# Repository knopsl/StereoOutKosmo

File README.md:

# Stereo output / Kosmo

Stereo output synthesizer module in Kosmo format.

This is somewhat based on the [Barton Stereo Outs](https://www.bartonmusicalcircuits.com/stereoouts/index.html)  module. There are four AC coupled inputs with pan and level controls. 

The headphone output section is based on the LM4808 datasheet circuit. This is an SMD (SOIC-8) part; all other components are through hole.

I've built this but my mechanical design was frankly stupid. I ended up kludging it together in a somewhat horrible way. I have eliminated the PCB design file and Gerbers from this repository; do better ones yourself! The circuit design is fine as far as I can see. So is the front panel except the slider mounting screws holes would be eliminated if I were to do it over.

## Photo

## Documentation:

* [Schematic](Docs/ao_output.pdf)
* [BOM](Docs/ao_output_bom.md)

## Submodules

This repo uses submodules aoKicad and Kosmo_panel, which provide needed libaries for KiCad. To clone:

```
git clone git@github.com:holmesrichards/audiomixer.git
git submodule init
git submodule update
```

Alternatively do

```
git clone --recurse-submodules git@github.com:holmesrichards/audiomixer.git
```

Or if you download the repository as a zip file, you must also click on the "aoKicad" and "Kosmo\_panel" links on the GitHub page (they'll have "@ something" after them) and download them as separate zip files which you can unzip into this repo's aoKicad and Kosmo\_panel directories.

If desired, copy the files from aoKicad and Kosmo\_panel to wherever you prefer (your KiCad user library directory, for instance, if you have one). Then in KiCad, add symbol libraries 

```
aoKicad/ao_symbols
Kosmo_panel/Kosmo
```
and footprint libraries 
```
aoKicad/ao_tht
Kosmo_panel/Kosmo_panel.
```

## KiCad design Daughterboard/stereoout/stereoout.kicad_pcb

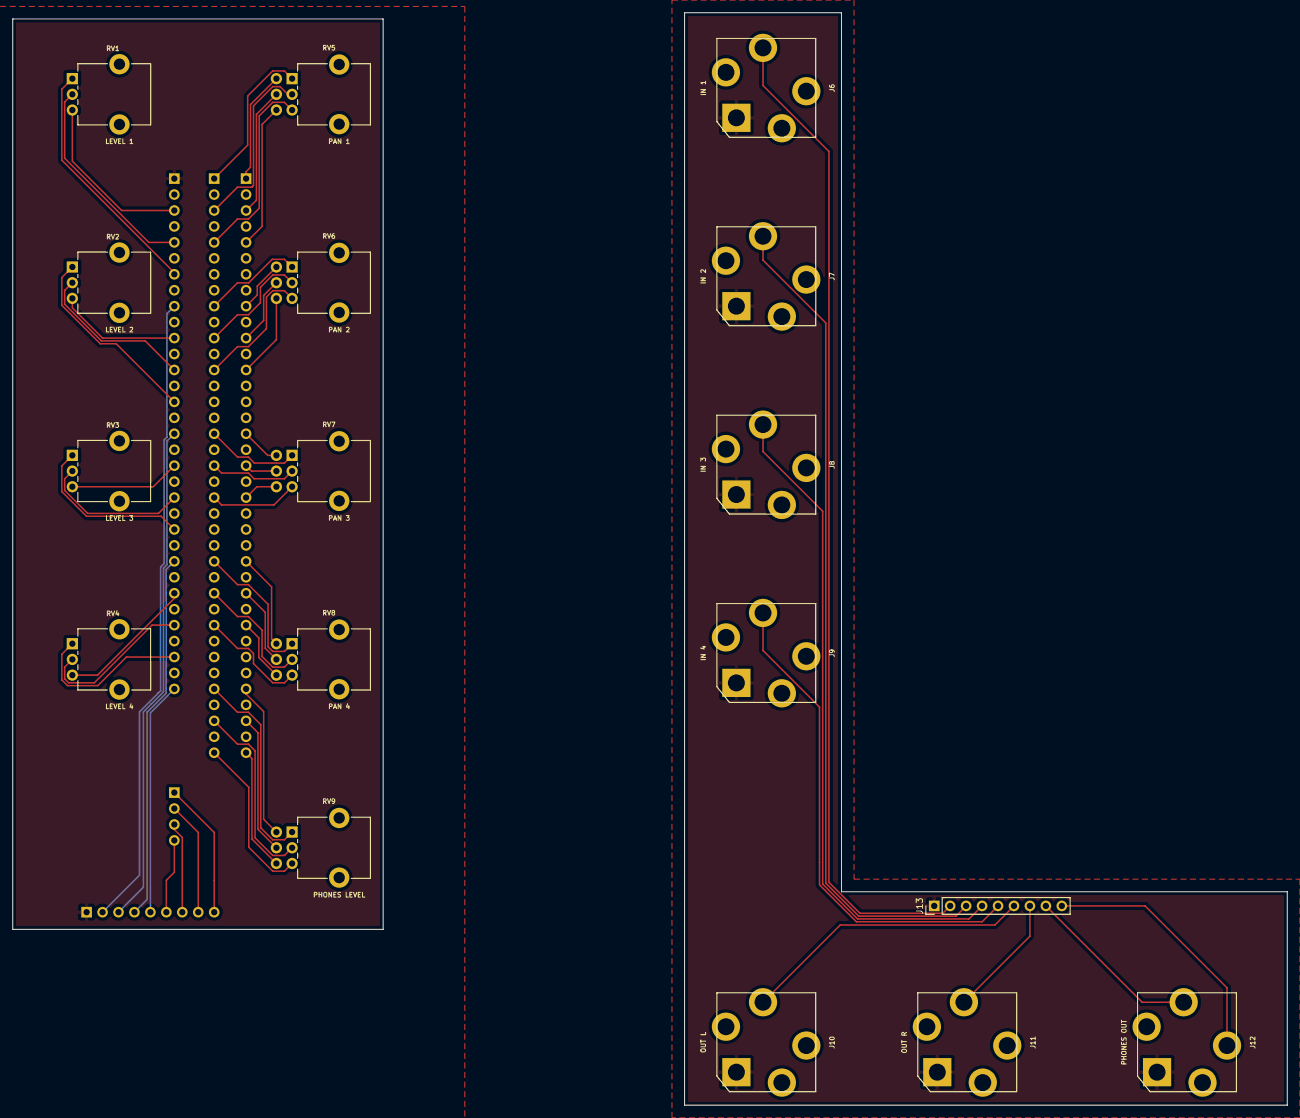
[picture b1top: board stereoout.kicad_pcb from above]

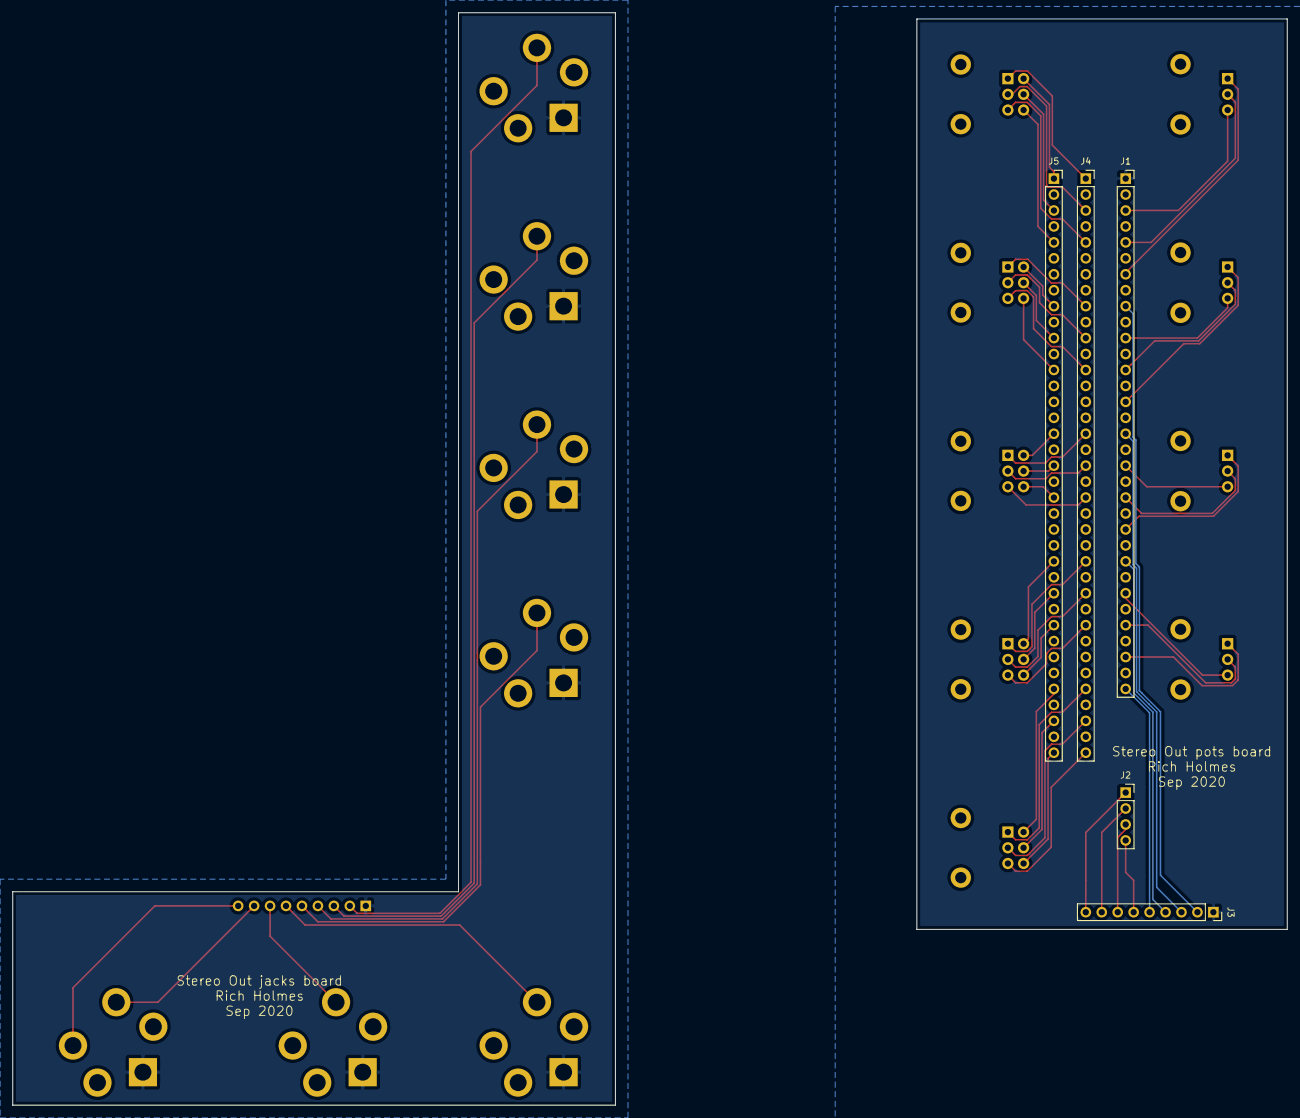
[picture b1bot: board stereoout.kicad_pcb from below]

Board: 2 copper layers, 203.0 x 174.0 mm, 22 parts (5 on the bottom side), 59 nets.

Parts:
J1: Conn_01x33; PinSocket_1x33_P2.54mm_Vertical
J2: Conn_01x04; PinSocket_1x04_P2.54mm_Vertical
J3: Conn_01x09; PinSocket_1x09_P2.54mm_Vertical
J4, J5: Conn_01x37; PinSocket_1x37_P2.54mm_Vertical
J6, J7, J8, J9, J10, J11: AudioJack2; Jack_6.35mm_PJ_629HAN
J12: AudioJack3; Jack_6.35mm_PJ_629HAN
J13: Conn_01x09; PinHeader_1x09_P2.54mm_Vertical
RV1, RV2, RV3, RV4: R_POT; Potentiometer_Alpha_RD901F-40-00D_Single_Vertical_CircularH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
RV5, RV6, RV7, RV8, RV9: R_POT; Potentiometer_Alpha_RD902F-40-00D_Dual_Vertical_CircularHol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

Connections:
/HL: J2.2, J3.8
/HR: J2.1, J3.9
/HVOL1_1: J4.33, RV9.1
/HVOL1_2: J4.35, RV9.2
/HVOL1_3: J4.37, RV9.3
/HVOL1_4: J5.33, RV9.4
/HVOL1_5: J5.35, RV9.5
/HVOL1_6: J5.37, RV9.6
/IN1: J1.9, J3.2
/IN2: J1.17, J3.3
/IN3: J1.25, J3.4
/IN4: J1.33, J3.5
/LEV1_1: J1.3, RV1.3
/LEV1_2: J1.5, RV1.2
/LEV1_3: J1.7, RV1.1
/LEV2_1: J1.11, RV2.3
/LEV2_2: J1.13, RV2.2
/LEV2_3: J1.15, RV2.1
/LEV3_1: J1.19, RV3.3
/LEV3_2: J1.21, RV3.2
/LEV3_3: J1.23, RV3.1
/LEV4_1: J1.27, RV4.3
/LEV4_2: J1.29, RV4.2
/LEV4_3: J1.31, RV4.1
/LO: J2.4, J3.6
/PAN1_1: J4.1, RV5.1
/PAN1_2: J4.3, RV5.2
/PAN1_3: J4.5, RV5.3
/PAN1_4: J5.1, RV5.4
/PAN1_5: J5.3, RV5.5
/PAN1_6: J5.5, RV5.6
/PAN2_1: J4.9, RV6.1
/PAN2_2: J4.11, RV6.2
/PAN2_3: J4.13, RV6.3
/PAN2_4: J5.9, RV6.4
/PAN2_5: J5.11, RV6.5
/PAN2_6: J5.13, RV6.6
/PAN3_1: J4.17, RV7.1
/PAN3_2: J4.19, RV7.2
/PAN3_3: J4.21, RV7.3
/PAN3_4: J5.17, RV7.4
/PAN3_5: J5.19, RV7.5
/PAN3_6: J5.21, RV7.6
/PAN4_1: J4.25, RV8.1
/PAN4_2: J4.27, RV8.2
/PAN4_3: J4.29, RV8.3
/PAN4_5: J5.25, RV8.4
/PAN4_6: J5.27, RV8.5
/RO: J2.3, J3.7
GND: J1.1, J3.1, J6.S, J7.S, J8.S, J9.S, J10.S, J11.S, J12.S, J13.1
unnamed: J5.29, RV8.6
unnamed: J10.T, J13.6
unnamed: J11.T, J13.7
unnamed: J12.R, J13.9
unnamed: J12.T, J13.8
unnamed: J6.T, J13.2
unnamed: J7.T, J13.3
unnamed: J8.T, J13.4
unnamed: J9.T, J13.5

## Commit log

2020-10-25 Finalize design and add Gerbers for first PCB run
2020-11-05 Fix wrong pot orientations and touch up routing
2020-11-30 README
2021-01-02 Footprints updated
2021-01-17 Include lib table files
2021-02-13 Slide pot version of panel
2021-02-19 Footprint update
2021-03-18 Rethink, make this a new design
2021-03-20 Rename file; PCB logos and text; more mounting holes
2021-03-20 Pot info added
2021-04-02 rm Barton Daughterboard directory; final changes before fabbing; Gerbers; docs updates
2021-04-02 There is no general level control
2021-04-10 Component value changes, BOM updates
2021-05-11 Deletions
2021-06-15 Reconnect pots, correct some values
2021-07-29 Gerbers
2021-08-07 Kosmo_panel lib update
2021-09-21 Libraries cleanup; rm PCB layout and Gerbers; rm images of other headphone outputs; update README and schematic
